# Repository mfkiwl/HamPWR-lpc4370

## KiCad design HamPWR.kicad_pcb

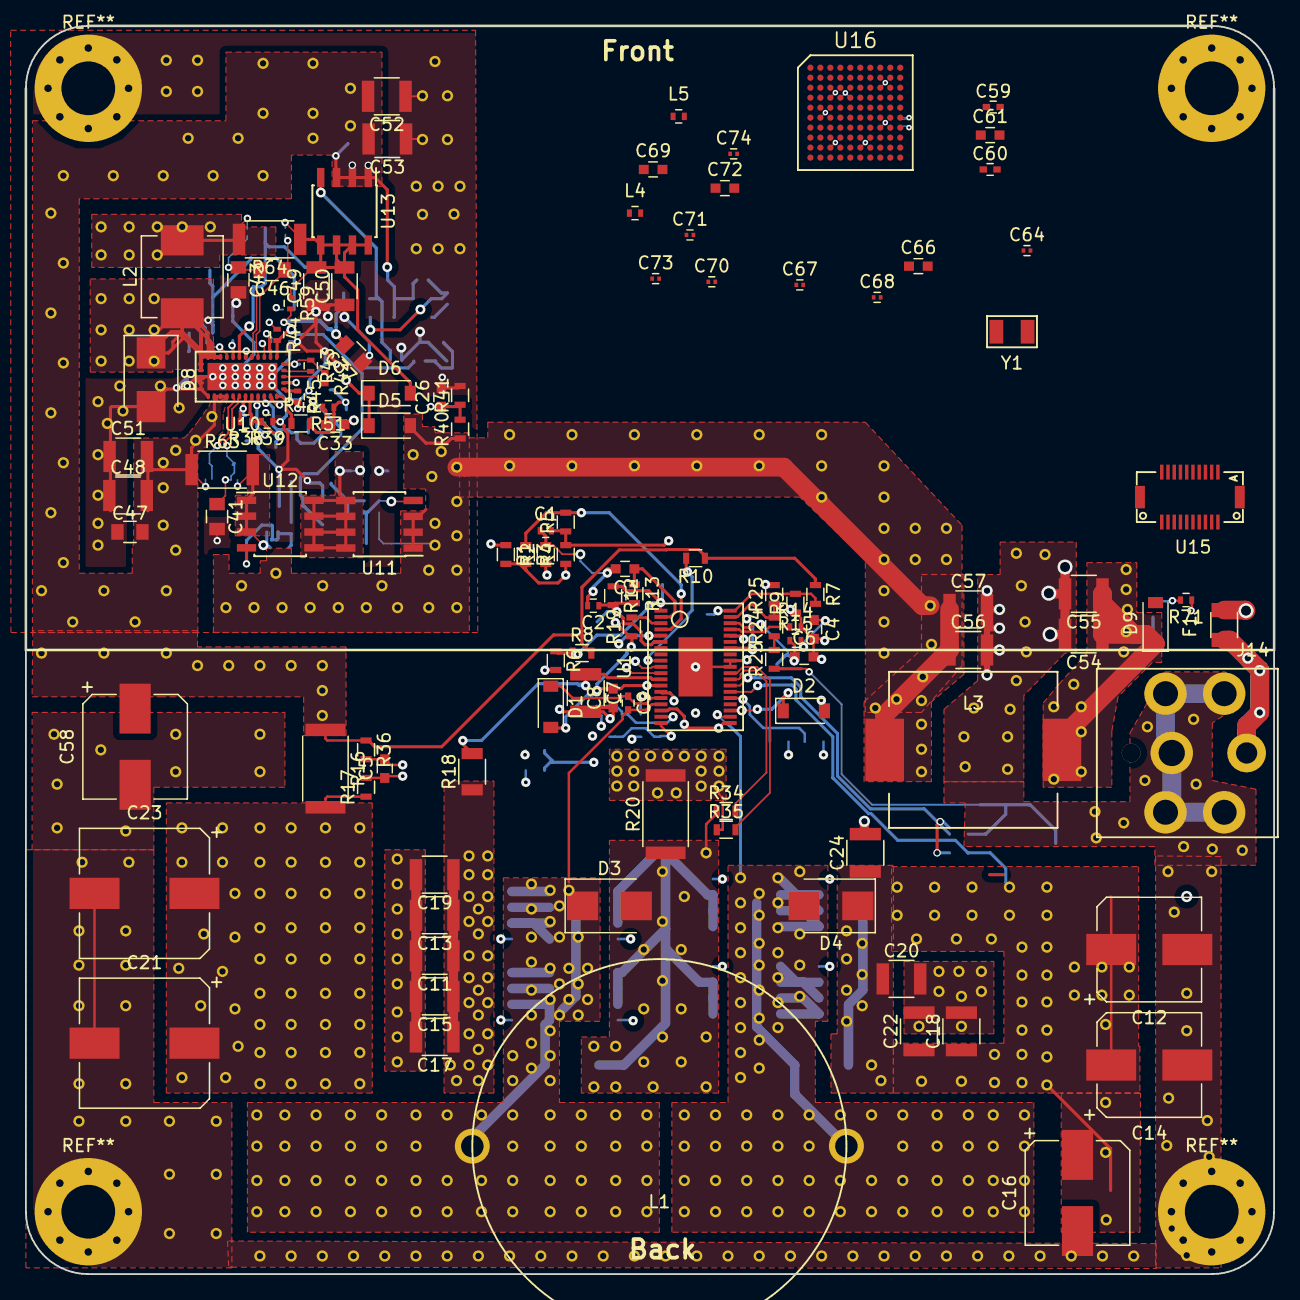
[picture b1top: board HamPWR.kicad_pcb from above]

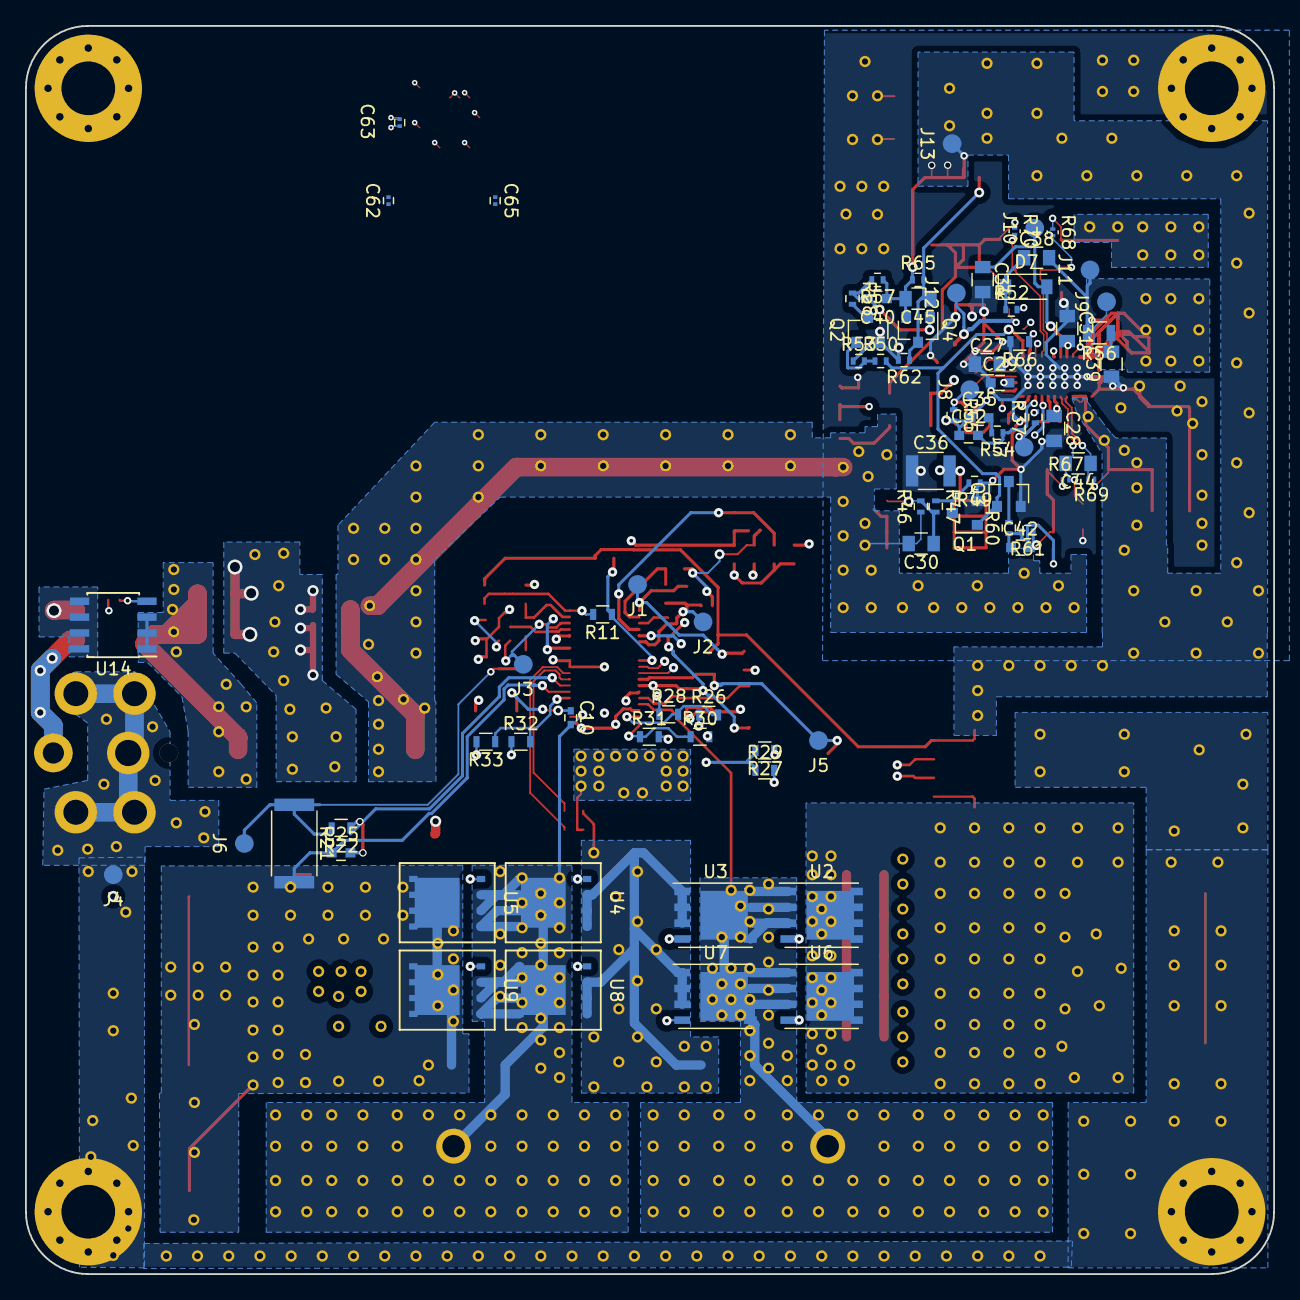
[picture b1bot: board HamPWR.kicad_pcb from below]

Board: 4 copper layers, 100.0 x 100.0 mm, 195 parts (79 on the bottom side), 95 nets.

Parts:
C1: 0.033µF; R_0402
C2: 0.1µF 6.3V; R_0402
C3, C4: 33nF; C_0603
C5: 0.47µF; C_0603
C6, C25, C40: DNP; C_0603
C7, C11: 1µF 100V; C_1210
C8: 4.7µF 10V; C_0603
C9, C10: 0.1µF; C_0402
C12, C14, C16, C58: 220µF 35V; CP_Elec_8x10.5
C13, C15: 4.7µF 100V; C_1210
C17, C19, C54, C55, C56, C57: 10µF 100V; C_1210
C18: 1µF 50V; C_1210
C20, C22, C24: 4.7µF 50V; C_1210
C21, C23: 47µF 80V; CP_Elec_10x10.5
C26, C42: 10nF; C_0603
C27, C28, C34, C47: 1µF 25V; C_0805
C29, C32: 51pF 50V; C_0603
C30, C41, C43, C44, C45, C46: 0.1µF; C_0805
C31, C37, C38: 0.1µF 50V; C_0805
C33: 130pF 50V; C_0603
C35: 2000pF 50V; C_0603
C36: DNP; C_1210
C39: DNP; C_0805
C48, C51, C52, C53: 10µF 25V; C_1210
C49, C50: 10µF 25V; C_1206
C59, C60: 20pF; C_0402
C61, C66, C69, C72: 10µF; C_0603
C62, C63, C67, C70, C73, C74: 100nF; C_0201
C64: 39nF; C_0201
C65, C71: 22nF; C_0201
C68: 3.3nF; C_0201
D1, D2: BAT46GW; D_SOD-123
D3, D4: STPS5L60; D_SMB
D5, D6, D7: BAT54; D_SOD-123
D8: DNP; D_SMB
D9: 10V; D_SOD-123
F1: 10A Fast, 0685H9100-01; Fuse_SMD1206_Reflow
J1: CTRL; Measurement_Point_Round-SMD-Pad_Small
J2: VREF; Measurement_Point_Round-SMD-Pad_Small
J3: VC; Measurement_Point_Round-SMD-Pad_Small
J4: GND; Measurement_Point_Round-SMD-Pad_Small
J5: VIN; Measurement_Point_Round-SMD-Pad_Small
J6: VOUT; Measurement_Point_Round-SMD-Pad_Small
J7: ICREF; Measurement_Point_Round-SMD-Pad_Small
J8: FBO; Measurement_Point_Round-SMD-Pad_Small
J9: BOOT; Measurement_Point_Round-SMD-Pad_Small
J10: VDDP; Measurement_Point_Round-SMD-Pad_Small
J11: PHASE; Measurement_Point_Round-SMD-Pad_Small
J12: VFB; Measurement_Point_Round-SMD-Pad_Small
J13: VSYS; Measurement_Point_Round-SMD-Pad_Small
J14: PJ-082BH; pj-082bh
L1: 2300HT-100-H-RC; 2300HT
L2: IHLP2525CZER3R3M01; L_Vishay_IHLP-2525
L3: SRP1265A-5R6M; SRP1265A
L4, L5: BLM15HG601SN1D; L_0402
Q1, Q2, Q3: 2N7002P; SOT-23
Q4: DMP10H4D2S; SOT-23
R1, R3, R4: 200k; R_0603
R2, R5, R12, R19, R22, R26, R27, R28, R29, R30, R31, R32, R33, R34, R35, R36, R48, R66: 0; R_0603
R6, R8, R11: DNP; R_0603
R7, R10: 499k; R_0603
R9: 27.4k; R_0603
R13: 100k; R_0603
R14: 147k 1%; R_0402
R15: 7.5k 5%; R_0402
R16: 0.0015 1%; R_2512
R17: 51 5%; R_0603
R18: 0; R_1206
R20: 0.002 1%; R_2512
R21: 0.008; R_2512
R23: 1.37k 1%; R_0603
R24: 71.5k 1%; R_0603
R25: 3.83k 1%; R_0603
R37: 1400k; R_0402
R38, R55: 200k; R_0402
R39: 49.9k; R_0402
R40: 430k; R_0603
R41: 66.5k; R_0603
R42, R43, R44, R45, R46, R47, R57, R58, R60, R61, R71: 10k; R_0402
R49: DNP; R_0402
R50: 1k; R_0402
R51: 4.7k; R_0402
R52: 3.9 1%; R_0402
R53: 1M; R_0402
R54: 7.5k; R_0402
R56: DNP; R_0805
R59: 100; R_0402
R62, R65: 100k; R_0402
R63: 0.010; R_2010
R64: 0.01; R_2010
R67, R68, R69, R70: 0; R_0201
U1: LT3790; TSSOP_38_EPAA
U2, U3, U6, U7: SQJ459EP; PowerPAK_SO-8_Single
U4, U5, U8, U9: BSC032N04LS; PG-TDSON-8
U10: bq24765; TI_RUV
U11, U12, U13, U14: Si4435DY; SOIC-8_3.9x4.9mm_Pitch1.27mm
U15: DF12; DF12-20DP
U16: LPC4370; BGA_100
Y1: FK135EIHM0.032768; FK135

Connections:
/BAT_CHG//ACDRV: C30.1, R46.2, R47.2, U11.4
/BAT_CHG//BATDRV: C45.1, Q4.3, R62.1, R65.2, U13.4
/BAT_CHG//BYPASS: C42.1, R60.1, R61.2, U12.4
/BAT_CHG/ACIN: C26.1, R40.2, R41.1, U10.9
/BAT_CHG/ACOK: Q1.1, Q3.1, R44.2, R50.2, U10.18
/BAT_CHG/BAT: C49.2, C50.2, D6.2, R59.1, R64.1, R70.1, U13.5, U13.6, U13.7, U13.8
/BAT_CHG/CE: R45.1, U10.13
/BAT_CHG/CSO_N: C46.1, R70.2, U10.21
/BAT_CHG/CSO_P: C43.1, C46.2, R68.2, U10.22
/BAT_CHG/CSS_N: C44.1, R69.2, U10.5
/BAT_CHG/CSS_P: C41.1, C44.2, R67.2, U10.6
/BAT_CHG/DCIN_A: C31.2, D5.1, D6.1, U10.25
/BAT_CHG/ICOUT: R37.2, U10.23
/BAT_CHG/ICREF: J7.1, R37.1, R38.1, R39.2, U10.8
/BAT_CHG/PHASE: C38.2, D8.1, J11.1, L2.1, R56.2, U10.27, U10.28, U10.29, U10.30, U10.31
/BAT_CHG/SCL: R43.2, U10.16
/BAT_CHG/SDA: R42.2, U10.15
/BAT_CHG/VDDSMB: C27.2, R42.1, R43.1, U10.17
/BAT_CHG/VICM: C29.2, U10.14
/BAT_CHG/VREF: C28.1, R38.2, R44.1, R45.2, U10.7
/DCDC_24V/BG1: R26.2, R28.2, U1.18
/DCDC_24V/BG2: R30.1, R31.1, U1.19
/DCDC_24V/BST2: C10.1, D2.1, U1.22
/DCDC_24V/C/10: R3.1, R5.2, U1.4
/DCDC_24V/CCM: C1.2, R4.2, R5.1, U1.32
/DCDC_24V/CTRL: J1.1, R6.1, R8.1, R12.1, U1.1
/DCDC_24V/FB: R24.2, R25.1, U1.37
/DCDC_24V/IL: C9.2, D3.1, L1.1, U1.16, U2.1, U2.2, U2.3, U3.5, U6.1, U6.2, U6.3, U7.5
/DCDC_24V/INTVCC: C8.2, D1.2, D2.2, R1.2, R3.2, R4.1, R19.1, U1.13
/DCDC_24V/IR: C10.2, D4.2, L1.2, U1.21, U4.5, U4.6, U4.7, U4.8, U4.9, U5.1, U5.2, U5.3, U8.5, U8.6, U8.7, U8.8, U8.9, U9.1, U9.2, U9.3
/DCDC_24V/ISN: C25.2, R22.1, U1.26
/DCDC_24V/ISP: C12.1, C14.1, C16.1, C18.1, C20.1, C22.1, C24.1, C25.1, D4.1, R21.2, U1.25, U5.5, U5.6, U5.7, U5.8, U5.9, U9.5, U9.6, U9.7, U9.8, U9.9
/DCDC_24V/IVIN_N: C5.1, R17.2, U1.11
/DCDC_24V/IVIN_P: C5.2, R36.2, U1.10
/DCDC_24V/OVLO: R7.2, R9.2, R11.2, U1.38
/DCDC_24V/PVIN: C40.1, C45.2, C47.2, C48.2, C51.2, C52.2, C53.2, C58.1, J13.1, Q4.2, R7.1, R8.2, R10.1, R16.1, R36.1, R57.1, R63.1, R65.1, R69.1, U10.2, U10.3, U10.4, U13.1, U13.2, U13.3
/DCDC_24V/SHORT: R1.1, U1.5
/DCDC_24V/SNS: D3.2, R20.1, R34.1, U3.1, U3.2, U3.3, U4.1, U4.2, U4.3, U7.1, U7.2, U7.3, U8.1, U8.2, U8.3
/DCDC_24V/SNS_N: R35.2, U1.28
/DCDC_24V/SNS_P: R34.2, U1.27
/DCDC_24V/SYNC: R2.1, U1.34
/DCDC_24V/TG1: R27.2, R29.1, U1.14
/DCDC_24V/TG2: R32.2, R33.1, U1.24
/DCDC_24V/VIN: C7.1, J5.1, R18.2, U1.12
/DCDC_24V/VOUT: J6.1, R21.1, R22.2, R23.1
/DCDC_24V/VREF: C2.1, J2.1, R12.2, R13.2, U1.6
/DCDC_24V/VTOP: C11.1, C13.1, C15.1, C17.1, C19.1, C21.1, C23.1, R16.2, R17.1, R18.1, U2.5, U6.5
/MCU_MAIN/VDDA: C74.1, L4.2, U16.B2
/MCU_MAIN/VDDREG: C70.1, C71.1, C72.1, L5.2, U16.E4, U16.E5, U16.F4
/MCU_MAIN/VIO_3V3: C61.2, C62.2, C63.1, C64.2, C65.1, C66.2, C67.1, C68.2, C69.1, L4.1, L5.1, U16.D1, U16.D2, U16.F10, U16.K5
/VIN: C30.2, C56.1, C57.1, D5.2, L3.2, R40.1, R46.1, U11.1, U11.2, U11.3
/VIN_ADAPTER: F1.1, J14.1
/VIN_PROT: C54.1, C55.1, D9.1, L3.1, U14.1, U14.2, U14.3
GND: C1.1, C2.2, C3.2, C4.2, C6.2, C7.2, C8.1, C11.2, C12.2, C13.2, C14.2, C15.2, C16.2, C17.2, C18.2, C19.2, C20.2, C21.2, C22.2, C23.2, C24.2, C26.2, C27.1, C28.2, C29.1, C31.1, C34.2, C36.1, C37.1, C39.1, C41.2, C43.2, C47.1, C48.1, C49.1, C50.1, C51.1, C52.1, C53.1, C54.2, C55.2, C56.2, C57.2, C58.2, C59.1, C60.1, C61.1, C62.1, C63.2, C64.1, C65.2, C66.1, C67.2, C68.1, C69.2, C70.2, C71.2, C72.2, C73.2, C74.2, D8.2, J4.1, J14.2, J14.3, Q1.2, Q2.2, Q3.2, R2.2, R6.2, R9.1, R14.2, R20.2, R25.2, R35.1, R39.1, R41.2, R49.1, R53.1, R62.2, R66.2, R71.1, U1.17, U1.20, U1.29, U1.30, U1.39, U10.1, U10.32, U10.33, U10.34, U10.35, U16.C2, U16.C8, U16.D3, U16.D4, U16.D5, U16.F2, U16.G8, U16.J3, U16.J6
GNDA: R66.1, U10.19
unnamed: C3.1, R13.1, U1.2
unnamed: C4.1, R15.2
unnamed: C6.1, J3.1, R15.1, U1.36
unnamed: C9.1, D1.1, U1.15
unnamed: C32.1, C33.1, C35.1, R55.2, U10.11
unnamed: C32.2, R54.1, U10.10
unnamed: C33.2, R51.2
unnamed: C34.1, D7.2, J10.1, U10.24
unnamed: C35.2, R54.2
unnamed: C36.2, U11.5, U11.6, U11.7, U11.8, U12.5, U12.6, U12.7, U12.8
unnamed: C37.2, J12.1, R59.2, U10.20
unnamed: C38.1, D7.1, R52.1
unnamed: C39.2, R56.1
unnamed: C40.2, Q4.1, R57.2, R58.1
unnamed: C42.2, R61.1, R63.2, R67.1, U12.1, U12.2, U12.3
unnamed: C59.2, U16.A5, Y1.2
unnamed: C60.2, U16.B5, Y1.1
unnamed: C73.1, U16.C5
unnamed: D9.2, R71.2, U14.4
unnamed: F1.2, U14.5, U14.6, U14.7, U14.8
unnamed: J8.1, R48.2, R51.1, R55.1
unnamed: J9.1, R52.2, U10.26
unnamed: L2.2, R64.2, R68.1
unnamed: Q1.3, R47.1, R49.2
unnamed: Q2.1, R50.1, R53.2
unnamed: Q2.3, R58.2
unnamed: Q3.3, R60.2
unnamed: R10.2, R11.1, U1.9
unnamed: R14.1, U1.35
unnamed: R19.2, U1.3
unnamed: R23.2, R24.1
unnamed: R26.1, U3.4
unnamed: R27.1, U6.4
unnamed: R28.1, U7.4
unnamed: R29.2, U2.4
unnamed: R30.2, U8.4
unnamed: R31.2, U4.4
unnamed: R32.1, U5.4
unnamed: R33.2, U9.4
unnamed: R48.1, U10.12

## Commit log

2018-05-22 Progress
2018-05-22 Added gitignore file
2018-05-22 Applied gitignore
2018-05-22 Removed lock file
